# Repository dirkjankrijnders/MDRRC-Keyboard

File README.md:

MDRRC-Keyboard
==============

PCB for MDRRC Keyboard

Arduino
-------

To use the LiquidCrystal display from arduino:

`LiquidCrystal lcd(A3, A2, A1, 13, 12, 11);`

Add the following to your arduino boards.txt to use the board from the arduino IDE:

```
MRDCC-keyboard_v.name=MRDCC keyboard (virgin)
MRDCC-keyboard_v.bootloader.low_fuses=0xe1
MRDCC-keyboard_v.bootloader.high_fuses=0xff
MRDCC-keyboard_v.bootloader.extended_fuses=0xd9
MRDCC-keyboard_v.upload.maximum_size=8192
MRDCC-keyboard_v.build.mcu=atmega8
MRDCC-keyboard_v.build.f_cpu=1000000L
MRDCC-keyboard_v.build.core=arduino
MRDCC-keyboard_v.build.variant=standard

MRDCC-keyboard.name=MRDCC keyboard
MRDCC-keyboard.bootloader.low_fuses=0xa4
MRDCC-keyboard.bootloader.high_fuses=0xd9
MRDCC-keyboard.bootloader.extended_fuses=0xd9
MRDCC-keyboard.upload.maximum_size=8192
MRDCC-keyboard.build.mcu=atmega8
MRDCC-keyboard.build.f_cpu=8000000L
MRDCC-keyboard.build.core=arduino
MRDCC-keyboard.build.variant=standard
```

LICENSE
-------

Both hardware and firmware are placed under the Creative Commons Attribution-ShareAlike 3.0 Unported License. See <http://creativecommons.org/licenses/by-sa/3.0/> and License.txt for more details.

Copyright 2013
Dirkjan Krijnders
<dirkjan@krijnders.net>

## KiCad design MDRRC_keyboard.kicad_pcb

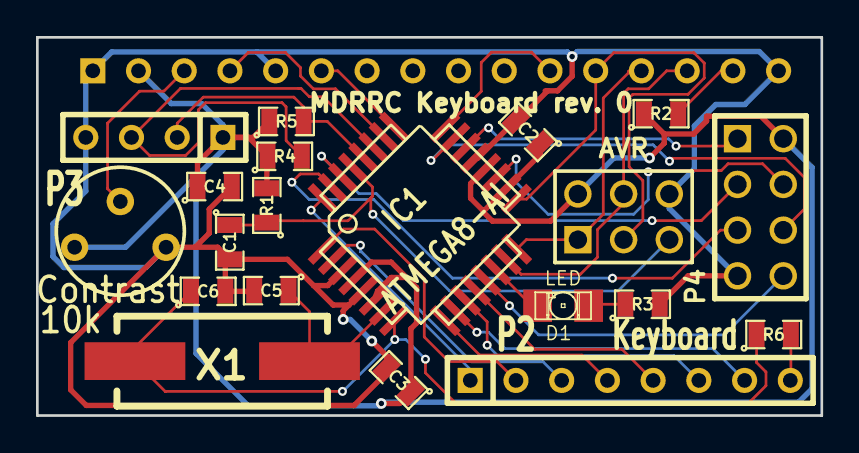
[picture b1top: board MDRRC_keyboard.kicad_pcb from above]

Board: 2 copper layers, 43.6 x 21.0 mm, 21 parts (1 on the bottom side), 31 nets.

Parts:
AVR: AVR-ISP-6; pin_array_3x2
C1, C2, C3, C4: 100nF; SM0805
C5, C6: C; SM0805
Contrast: 10k; RV2
D1: LED; LED-1206
IC1: ATMEGA8-AI; TQFP32
P1: LCD; SIL-16
P2: Keyboard; SIL-8
P3: CONN_4; SIL-4
P4: CONN_4X2; pin_array_4x2
R1, R4, R5: 10k; SM0805
R2: 4k7; SM0805
R3: 1k; SM0805
R6: 0; SM0805
X1: CRYSTAL; Crystal_HC49-SD_SMD_RevA_09Aug2010

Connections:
/SCL: IC1.28, P3.2, R5.2
/SDA: IC1.27, P3.3, R4.2
GND: AVR.6, C1.2, C2.2, C3.2, C4.2, C5.2, C6.2, Contrast.3, IC1.3, IC1.5, IC1.21, P1.1, P1.5, P1.16, P3.4, P4.7, R3.2
MISO: AVR.1, IC1.16, P1.13
MOSI: AVR.4, IC1.15, P1.14
unnamed: P2.8, R6.2
unnamed: D1.2, IC1.14
unnamed: C6.1, IC1.8, R6.1, X1.2
unnamed: C5.1, IC1.7, X1.1
unnamed: P1.15, R2.2
unnamed: IC1.30, P4.3
unnamed: IC1.31, P4.5
unnamed: IC1.19, P4.4
unnamed: IC1.22, P4.1
unnamed: IC1.11, P2.6
unnamed: IC1.24, P1.11
unnamed: IC1.25, P1.6
unnamed: IC1.26, P1.4
unnamed: Contrast.2, P1.3
unnamed: IC1.9, P2.4
unnamed: IC1.2, P2.3
unnamed: IC1.1, P2.2
unnamed: IC1.32, P2.1
unnamed: IC1.10, P2.7
unnamed: IC1.12, P2.5
unnamed: D1.1, R3.1
unnamed: AVR.5, C1.1, IC1.29, R1.1
PB1: IC1.13, P4.8
PC0: IC1.23, P4.6
SCK: AVR.3, IC1.17, P1.12
VCC: AVR.2, C2.1, C3.1, C4.1, Contrast.1, IC1.4, IC1.6, IC1.18, IC1.20, P1.2, P3.1, P4.2, R1.2, R2.1, R4.1, R5.1

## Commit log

2013-09-29 Schematic complete
2013-09-29 Fixed two small errors
2013-09-29 First board design
2013-09-29 Added possibility for crystal and broke out remaining I/O to header
2013-10-01 Updated board to include previous changes to schematic
2013-10-01 Silkscreen update, rev 0
2013-10-02 Added license remark
2014-03-09 Added some Arduino notes to readme.md
